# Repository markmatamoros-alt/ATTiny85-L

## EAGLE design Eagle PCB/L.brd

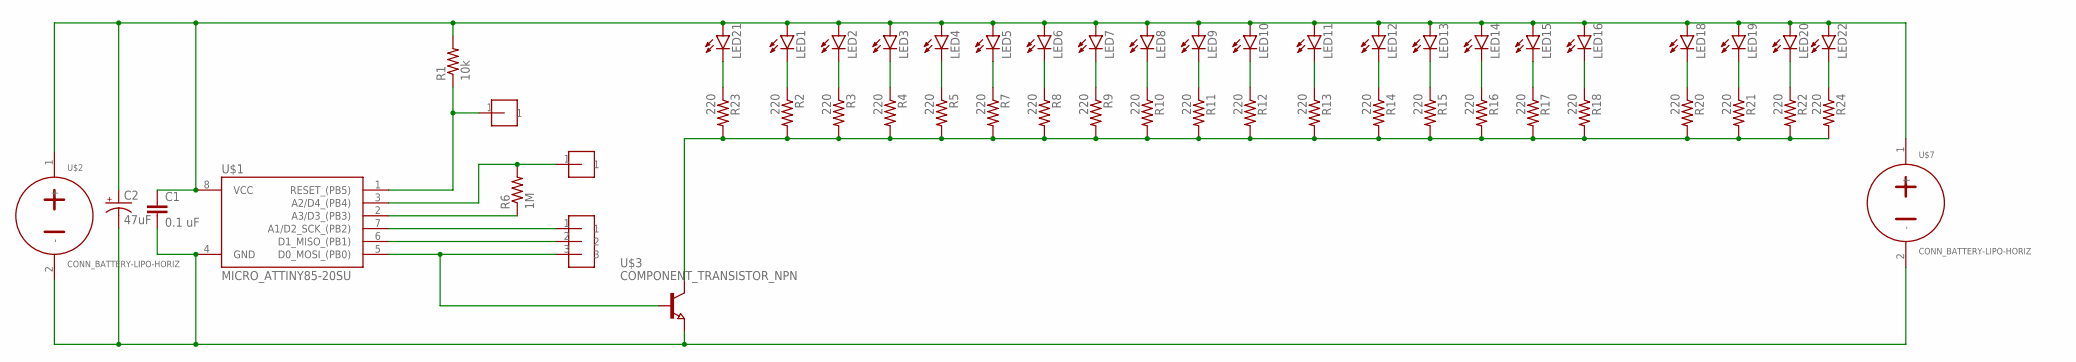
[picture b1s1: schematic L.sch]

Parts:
C1: 0.1 uF; 0805
C2: 47uF; CAP_RADIAL_CAN_10MM
LED1, LED2, LED3, LED4, LED5, LED6, LED7, LED8, LED9, LED10, LED11, LED12, LED13, LED14, LED15, LED16, LED18, LED19, LED20, LED21, LED22: LED-0805; CHIP-LED0805
R1: 10k; 0805
R2, R3, R4, R5, R7, R8, R9, R10, R11, R12, R13, R14, R15, R16, R17, R18, R20, R21, R22, R23, R24: 220; 0805
R6: 1M; 0805
U$1: MICRO_ATTINY85-20SU; SOIC8
U$2, U$7: CONN_BATTERY-LIPO-HORIZ; JST-PH-2-SMT-RA
U$3: COMPONENT_TRANSISTOR_NPN; SOT23
U$4, U$5: HEADER-1-TESTPOINT; TESTPOINT-1
U$6: HEADER-3-TESTPOINT; TESTPOINT-3

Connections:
unnamed: R1.1, U$1.1 (RESET_(PB5)), U$5.1
unnamed: C1.1, C2.+, LED1.A, LED2.A, LED3.A, LED4.A, LED5.A, LED6.A, LED7.A, LED8.A, LED9.A, LED10.A, LED11.A, LED12.A, LED13.A, LED14.A, LED15.A, LED16.A, LED18.A, LED19.A, LED20.A, LED21.A, LED22.A, R1.2, U$1.8 (VCC), U$2.1 (+), U$7.1 (+)
unnamed: LED22.C, R24.1
unnamed: LED4.C, R5.1
unnamed: LED3.C, R4.1
unnamed: LED2.C, R3.1
unnamed: LED1.C, R2.1
unnamed: R2.2, R3.2, R4.2, R5.2, R7.2, R8.2, R9.2, R10.2, R11.2, R12.2, R13.2, R14.2, R15.2, R16.2, R17.2, R18.2, R20.2, R21.2, R22.2, R23.2, R24.2, U$3.3 (C)
unnamed: U$1.7 (A1/D2_SCK_(PB2)), U$6.1
unnamed: R6.2, U$1.3 (A2/D4_(PB4)), U$4.1
unnamed: R6.1, U$1.2 (A3/D3_(PB3))
unnamed: U$1.6 (D1_MISO_(PB1)), U$6.2
unnamed: U$1.5 (D0_MOSI_(PB0)), U$3.1 (B), U$6.3
unnamed: LED21.C, R23.1
unnamed: LED5.C, R7.1
unnamed: C1.2, C2.-, U$1.4 (GND), U$2.2 (-), U$3.2 (E), U$7.2 (-)
unnamed: LED9.C, R11.1
unnamed: LED8.C, R10.1
unnamed: LED7.C, R9.1
unnamed: LED6.C, R8.1
unnamed: LED10.C, R12.1
unnamed: LED14.C, R16.1
unnamed: LED13.C, R15.1
unnamed: LED12.C, R14.1
unnamed: LED11.C, R13.1
unnamed: LED15.C, R17.1
unnamed: LED19.C, R21.1
unnamed: LED18.C, R20.1
unnamed: LED16.C, R18.1
unnamed: LED20.C, R22.1

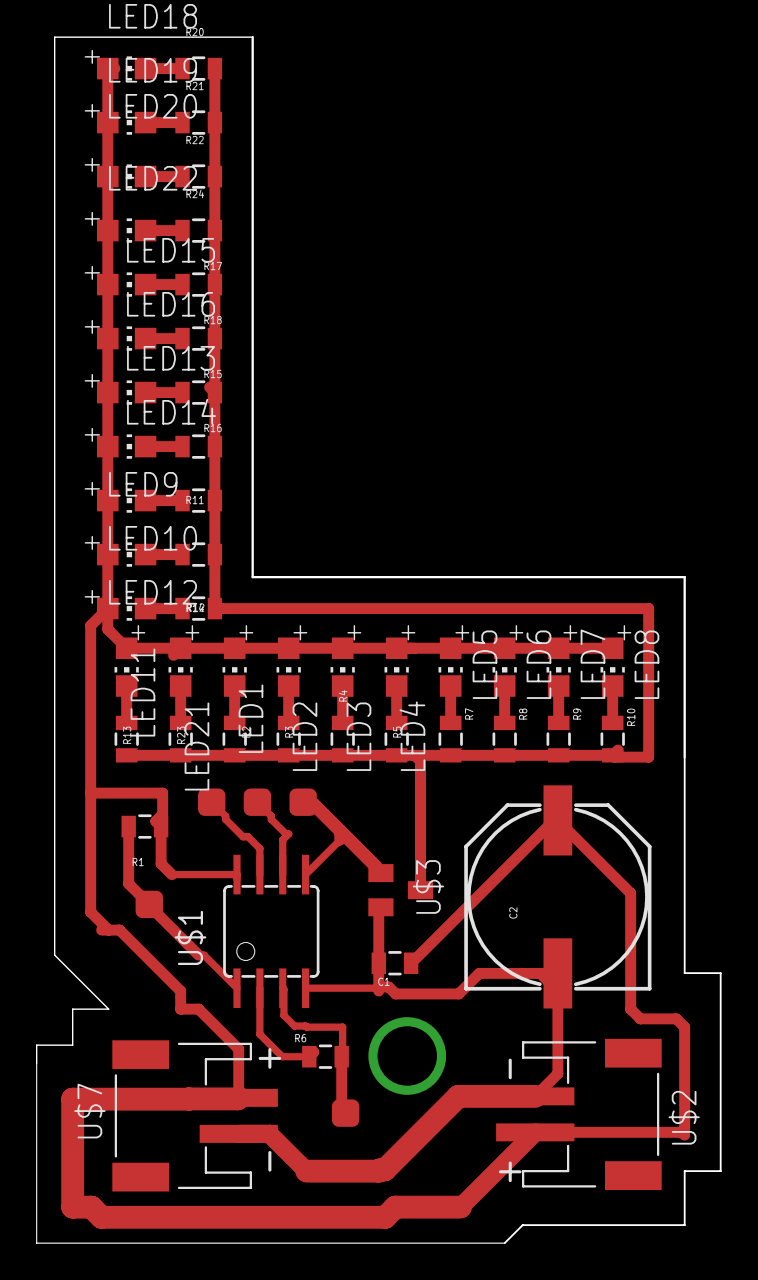
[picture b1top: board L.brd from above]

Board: 2 copper layers, 38.0 x 67.0 mm, 53 parts (0 on the bottom side), 30 nets.
